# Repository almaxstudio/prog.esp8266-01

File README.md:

# prog.esp8266-01
A base programmer for esp8266-01
It is a first test! Not tested

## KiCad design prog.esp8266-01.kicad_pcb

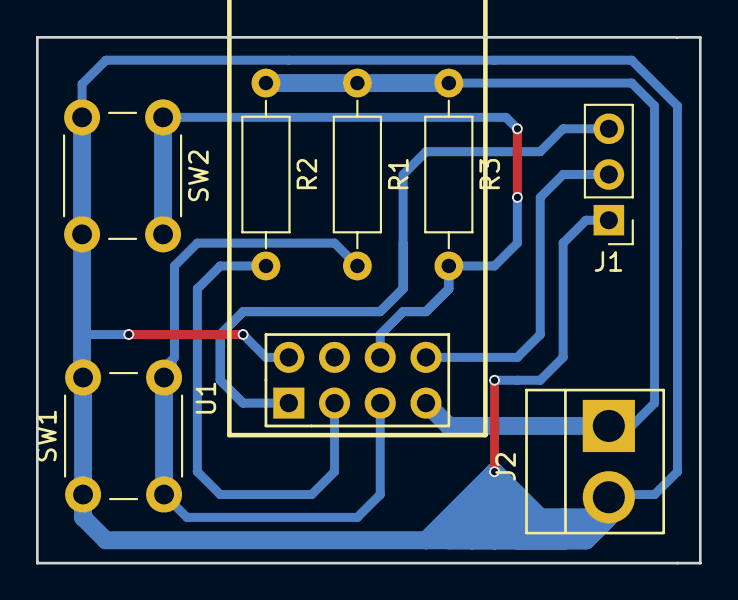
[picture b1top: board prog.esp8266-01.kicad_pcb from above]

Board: 2 copper layers, 36.8 x 29.2 mm, 8 parts (0 on the bottom side), 7 nets.

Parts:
J1: SERIAL; Pin_Header_Straight_1x03_Pitch2.54mm
J2: Power; Pin_Header_Straight_1x02_Pitch3.96mm_Friction_Lock
R1, R2, R3: 10K; R_Axial_DIN0207_L6.3mm_D2.5mm_P10.16mm_Horizontal
SW1: Reset; SW_PUSH_6mm
SW2: PROG; SW_PUSH_6mm
U1: ESP-01v090; ESP-01

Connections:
+3V3: J2.1, R1.1, R2.1, R3.1, U1.7
GNDREF: J1.1, J2.2, SW1.1, SW2.2, U1.2
unnamed: J1.2, U1.8
unnamed: J1.3, U1.1
unnamed: R1.2, SW1.2, U1.5
unnamed: R2.2, U1.3
unnamed: R3.2, SW2.1, U1.6

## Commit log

2017-06-22 First commit
    First commit
2017-06-23 last version
    Variate alcune dimensioni delle piste
